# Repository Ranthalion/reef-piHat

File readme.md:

View this project on [CADLAB.io](https://cadlab.io/project/1832). 

# reef-piHat
RPI Hat for reef-pi

Supports
 - Back powering the rpi with 5v
 - 9 channels of PWM control via PCA9685 (split between 3 connectors)
 - 3 channels for 1 wire communication (up to 3 DS18B20 temperature probes)
 - 2 i2c ports for ph probe modules
 - 2 ATO sensors
 - 8 channel 12v relay control via ULN2803
 - 8 GPIO breakout (intended for 3.3v relay module)

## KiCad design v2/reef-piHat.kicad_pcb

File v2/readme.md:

# reef-piHat
RPI Hat for reef-pi

Supports
 - Back powering the rpi with 5v
 - 12 channels of PWM control via PCA9685 (split between 4 connectors) with address selection
 - 3 channels for 1 wire communication (up to 3 DS18B20 temperature probes)
 - 2 i2c ports for ph probe modules
 - 2 ATO sensors with input protection
 - 8 channel 12v relay control via ULN2803
 - 8 GPIO breakout with input and output protection

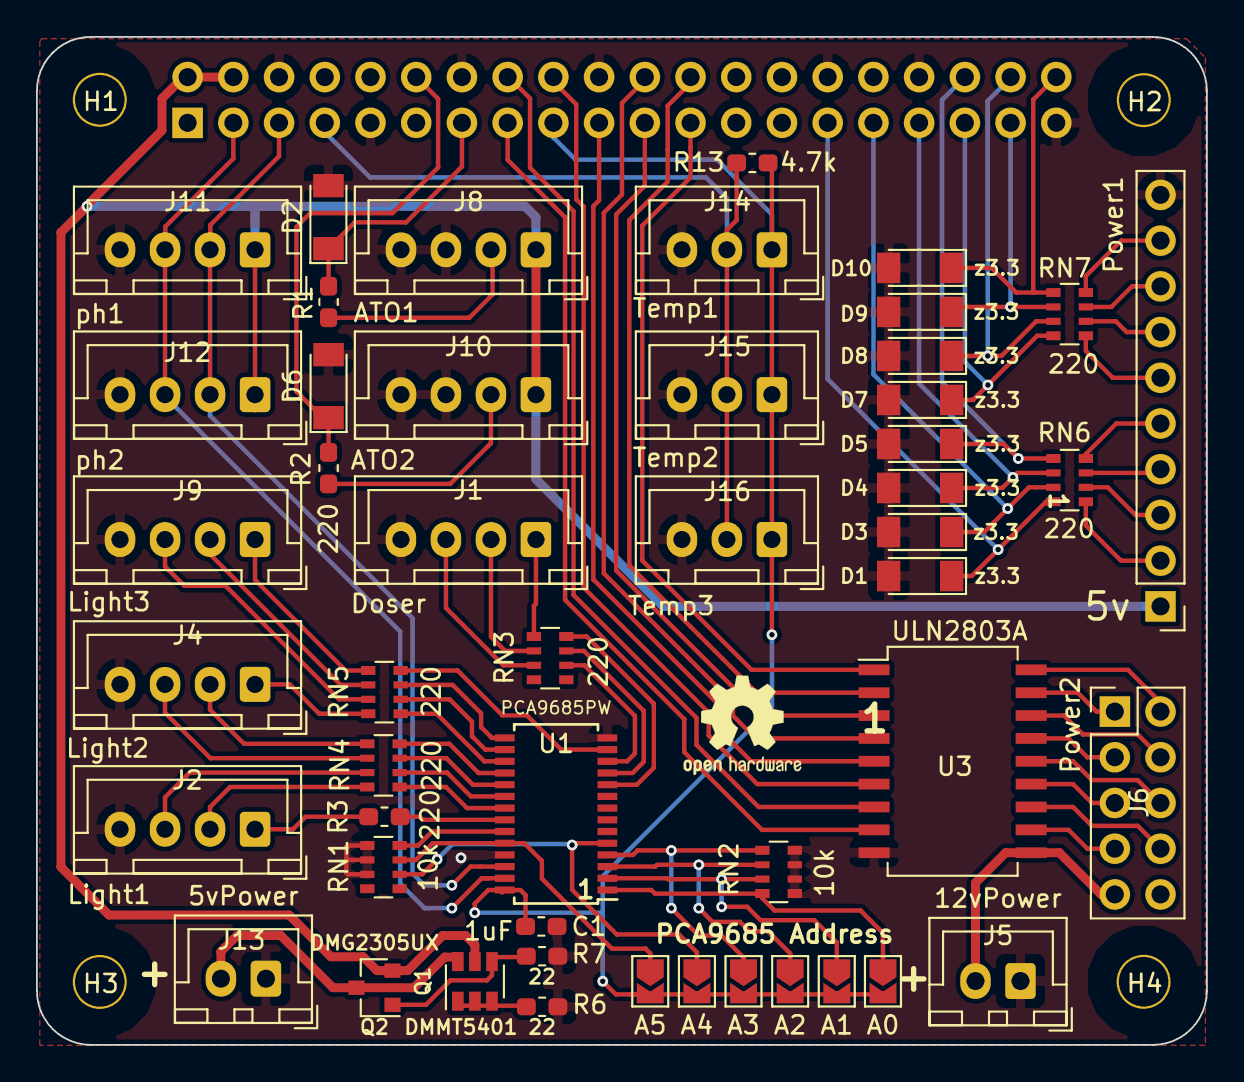
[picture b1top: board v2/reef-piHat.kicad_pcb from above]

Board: 2 copper layers, 65.0 x 56.0 mm, 54 parts (1 on the bottom side), 77 nets.

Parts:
A0, A1, A2, A3, A4, A5: NO; SolderJumper-2_P1.3mm_Open_TrianglePad1.0x1.5mm
C1: 1uF; C_0603_1608Metric_Pad1.05x0.95mm_HandSolder
D1, D2, D3, D4, D5, D6, D7, D8, D9, D10: z3.3; D_MiniMELF
H1, H2, H3, H4: 3mm_Mounting_Hole; NPTH_3mm_ID
J1: Doser; JST_XH_B04B-XH-A_1x04_P2.50mm_Vertical
J2: Light1; JST_XH_B04B-XH-A_1x04_P2.50mm_Vertical
J3: 40HAT; PinSocket_2x20_P2.54mm_Vertical
J4: Light2; JST_XH_B04B-XH-A_1x04_P2.50mm_Vertical
J5: 12vPower; JST_XH_B02B-XH-A_1x02_P2.50mm_Vertical
J6: Power2; PinHeader_2x05_P2.54mm_Vertical
J7: Power1; PinHeader_1x10_P2.54mm_Vertical
J8: ATO1; JST_XH_B04B-XH-A_1x04_P2.50mm_Vertical
J9: Light3; JST_XH_B04B-XH-A_1x04_P2.50mm_Vertical
J10: ATO2; JST_XH_B04B-XH-A_1x04_P2.50mm_Vertical
J11: ph1; JST_XH_B04B-XH-A_1x04_P2.50mm_Vertical
J12: ph2; JST_XH_B04B-XH-A_1x04_P2.50mm_Vertical
J13: 5vPower; JST_XH_B02B-XH-A_1x02_P2.50mm_Vertical
J14: Temp1; JST_XH_B03B-XH-A_1x03_P2.50mm_Vertical
J15: Temp2; JST_XH_B03B-XH-A_1x03_P2.50mm_Vertical
J16: Temp3; JST_XH_B03B-XH-A_1x03_P2.50mm_Vertical
Q1: DMMT5401; SOT-23-6
Q2: DMG2305UX; SOT-23
R1, R2, R3: 220; R_0603_1608Metric_Pad1.05x0.95mm_HandSolder
R6, R7: 22; R_0603_1608Metric_Pad1.05x0.95mm_HandSolder
R13: 4.7k; R_0603_1608Metric_Pad1.05x0.95mm_HandSolder
RN1, RN2: 10k; R_Array_Convex_4x0603
RN3, RN4, RN5, RN6, RN7: 220; R_Array_Convex_4x0603
U1: PCA9685PW; TSSOP-28_4.4x9.7mm_P0.65mm
U3: ULN2803A; SOP-18_7.0x12.5mm_P1.27mm

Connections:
/1WIRE: J3.7, J14.2, J15.2, J16.2, R13.1
/12V: J5.1, J6.9, U3.10
/A0: A0.1, RN2.8, U1.1
/A1: A1.1, RN2.7, U1.2
/A2: A2.1, RN2.6, U1.3
/A3: A3.1, RN2.5, U1.4
/A4: A4.1, RN1.6, U1.5
/A5: A5.1, RN1.7, U1.24
/ATO1: D2.1, J3.13, R1.2
/ATO2: D6.1, J3.12, R2.2
/LED4: RN3.8, U1.10
/LED5: RN3.7, U1.11
/LED6: RN3.6, U1.12
/LED7: RN5.8, U1.13
/LED8: RN5.7, U1.15
/LED9: RN5.6, U1.16
/LED10: RN5.5, U1.17
/LED11: RN4.8, U1.18
/LED12: RN4.7, U1.19
/LED13: RN4.6, U1.20
/LED14: RN4.5, U1.21
/LED15: R3.1, U1.22
/OE: RN1.8, U1.23
/P3V3_HAT: A0.2, A1.2, A2.2, A3.2, A4.2, A5.2, C1.1, J3.17, J14.1, J15.1, J16.1, R13.2, U1.28
/P5V: J13.2, Q1.6, Q2.3
/P5V_HAT: J3.2, J3.4, J7.1, J8.1, J10.1, J11.1, J12.1, Q1.5, Q2.2
/PA1: J3.23, U3.1
/PA2: J3.24, U3.2
/PA3: J3.21, U3.3
/PA4: J3.22, U3.4
/PA5: J3.19, U3.5
/PA6: J3.18, U3.6
/PA7: J3.16, U3.7
/PA8: J3.15, U3.8
/PA_O1: J6.2, U3.18
/PA_O2: J6.1, U3.17
/PA_O3: J6.4, U3.16
/PA_O4: J6.3, U3.15
/PA_O5: J6.6, U3.14
/PA_O6: J6.5, U3.13
/PA_O7: J6.8, U3.12
/PA_O8: J6.7, U3.11
/PB1: D10.1, J3.40, RN7.1
/PB2: D9.1, J3.37, RN7.2
/PB3: D8.1, J3.38, RN7.3
/PB4: D7.1, J3.35, RN7.4
/PB5: D5.1, J3.36, RN6.1
/PB6: D4.1, J3.33, RN6.2
/PB7: D3.1, J3.31, RN6.3
/PB8: D1.1, J3.29, RN6.4
/SCL: J3.5, J11.2, J12.2, U1.26
/SDA: J3.3, J11.3, J12.3, U1.27
GND: C1.2, D1.2, D2.2, D3.2, D4.2, D5.2, D6.2, D7.2, D8.2, D9.2, D10.2, J1.4, J2.4, J3.6, J3.9, J3.14, J3.20, J3.25, J3.30, J3.34, J3.39, J4.4, J5.2, J7.10, J8.3, J8.4, J9.4, J10.3, J10.4, J11.4, J12.4, J13.1, J14.3, J15.3, J16.3, R6.2, R7.2, RN1.1, RN1.2, RN1.3, RN2.1, RN2.2, RN2.3, RN2.4, U1.14, U1.25, U3.9
unnamed: J1.1, RN3.1
unnamed: J1.2, RN3.2
unnamed: J1.3, RN3.3
unnamed: J2.1, R3.2
unnamed: J2.2, RN4.4
unnamed: J2.3, RN4.3
unnamed: J4.1, RN5.4
unnamed: J4.2, RN4.1
unnamed: J4.3, RN4.2
unnamed: J7.2, RN6.5
unnamed: J7.3, RN6.6
unnamed: J7.4, RN6.7
unnamed: J7.5, RN6.8
unnamed: J7.6, RN7.5
unnamed: J7.7, RN7.6
unnamed: J7.8, RN7.7
unnamed: J7.9, RN7.8
unnamed: J8.2, R1.1
unnamed: J9.1, RN5.1
unnamed: J9.2, RN5.2
unnamed: J9.3, RN5.3
unnamed: J10.2, R2.1
unnamed: Q1.1, Q1.2, Q1.3, R6.1
unnamed: Q1.4, Q2.1, R7.1

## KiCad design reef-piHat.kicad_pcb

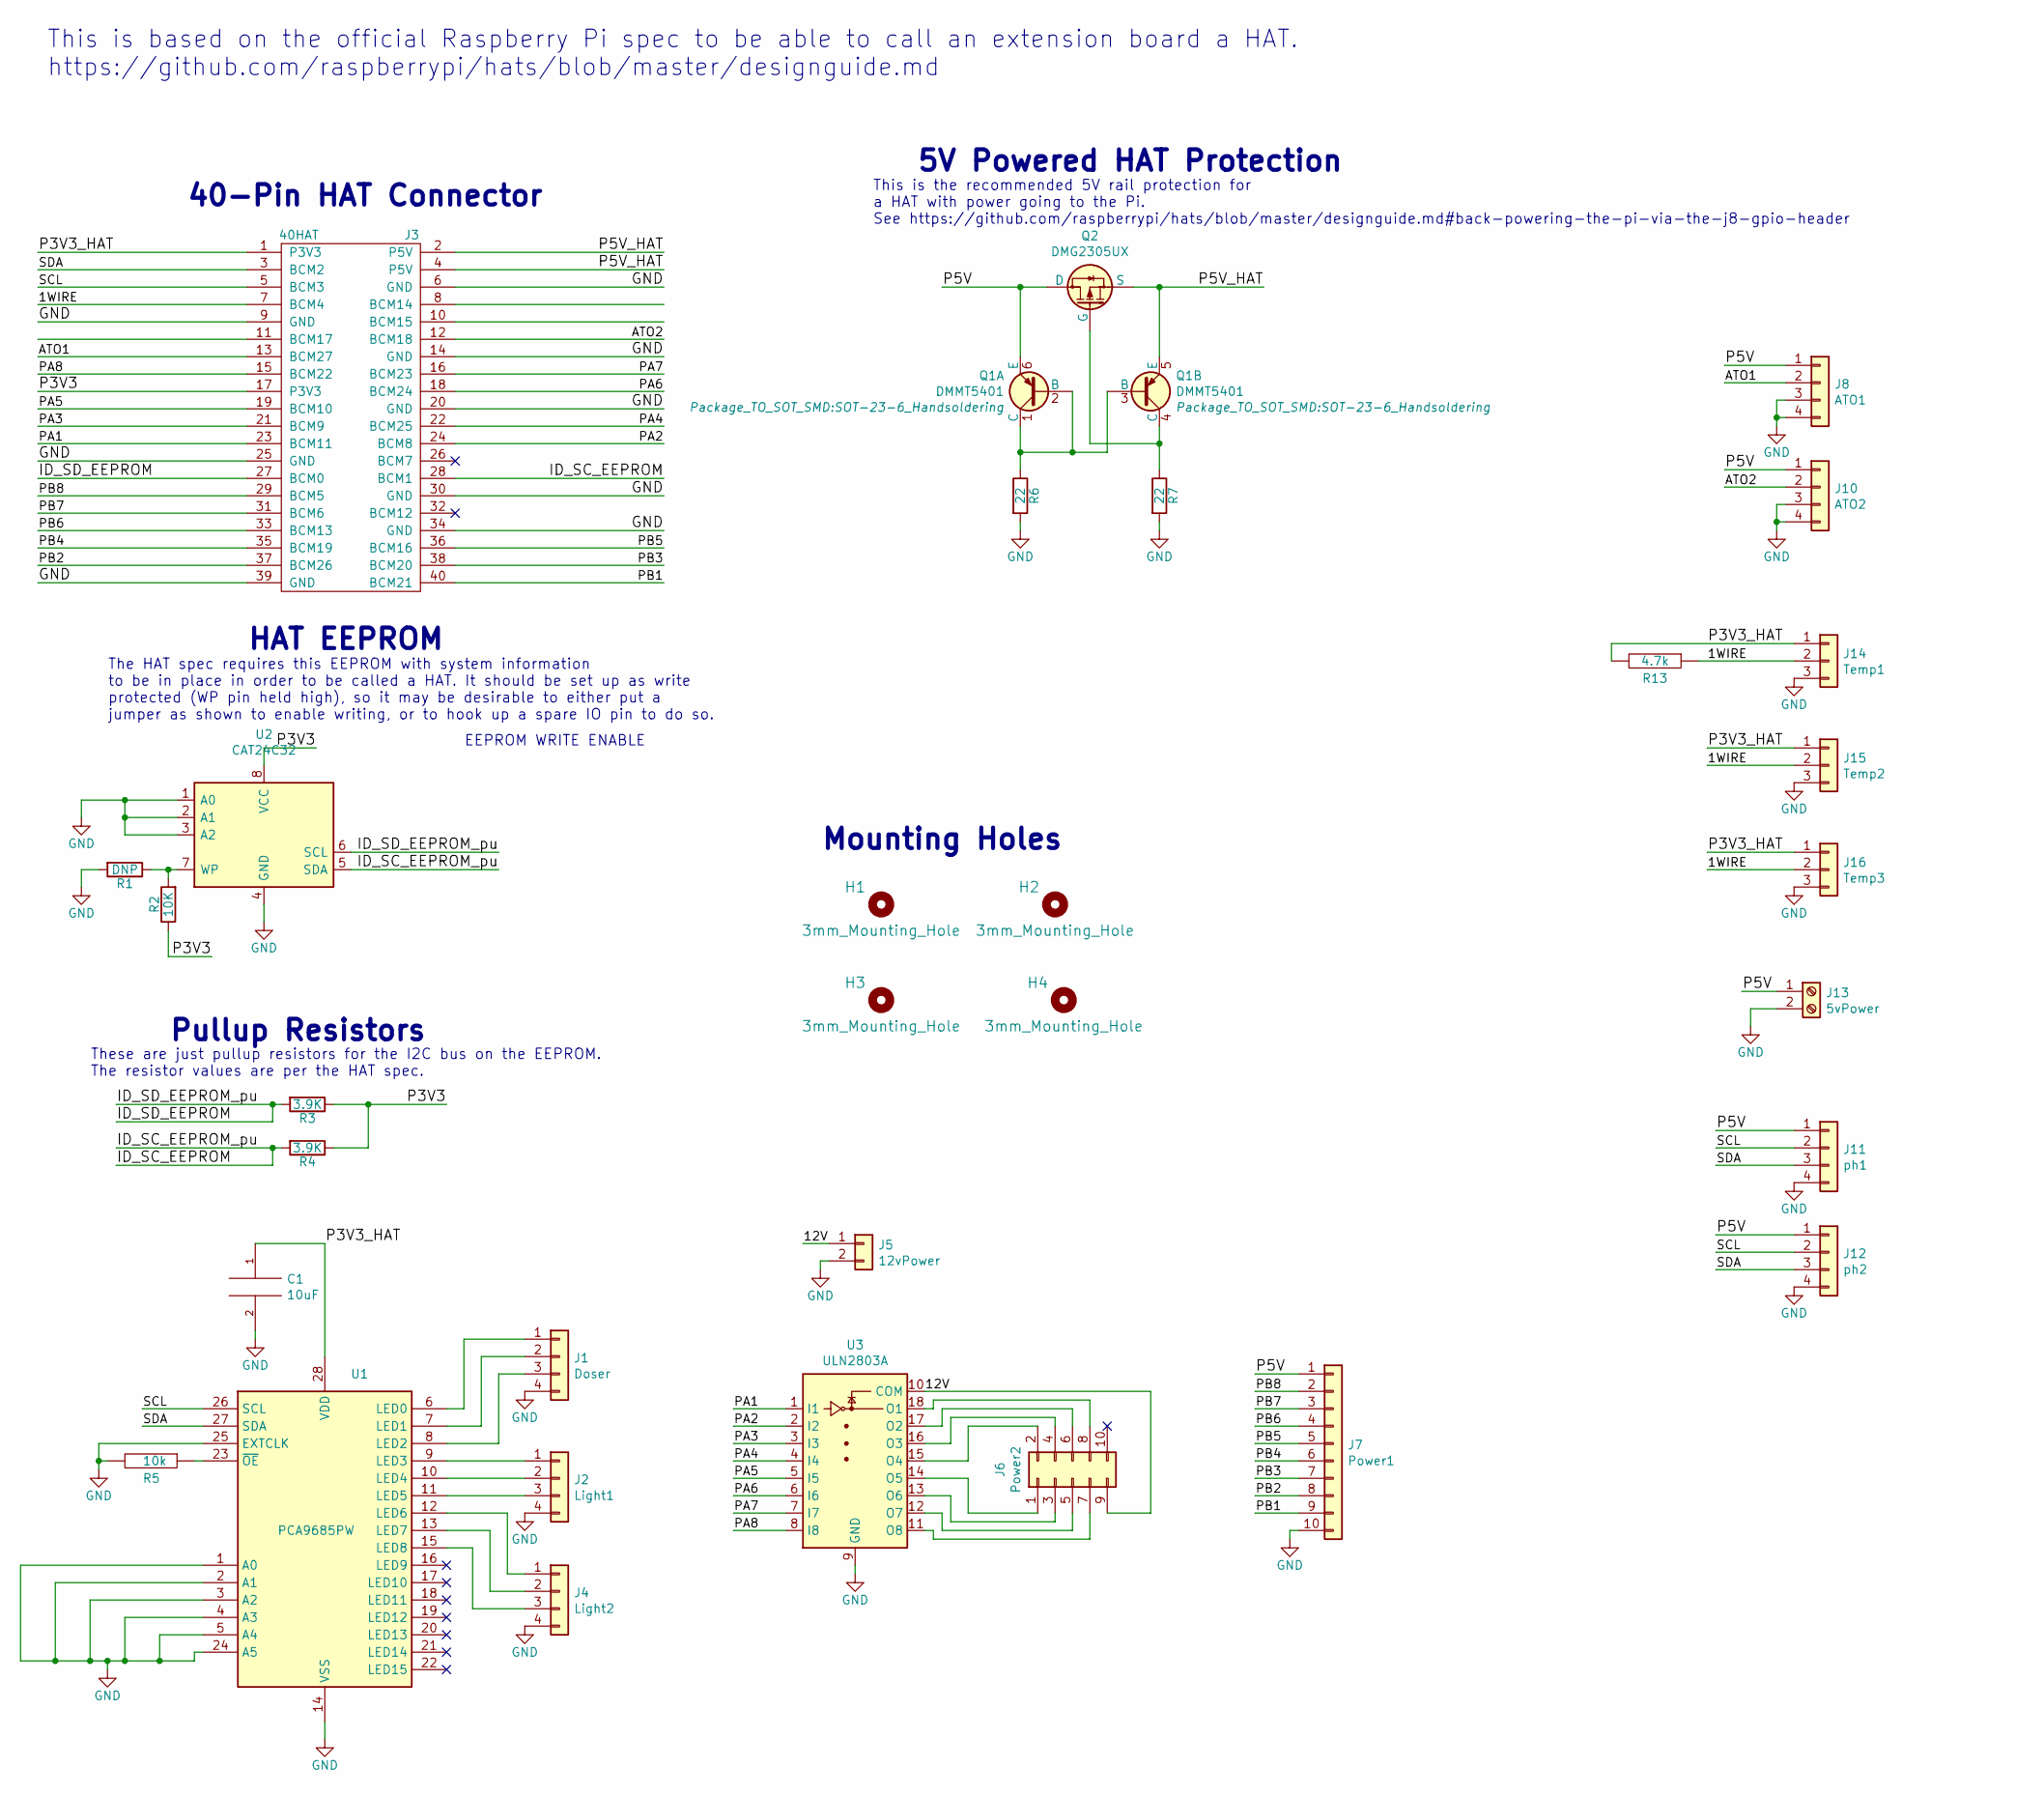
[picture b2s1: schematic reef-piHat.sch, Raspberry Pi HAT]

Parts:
C1: 10uF; C_1206_3216Metric_Pad1.42x1.75mm_HandSolder
H1, H2, H3, H4: 3mm_Mounting_Hole; NPTH_3mm_ID
J1: Doser; JST_XH_B04B-XH-A_1x04_P2.50mm_Vertical
J2: Light1; JST_XH_B04B-XH-A_1x04_P2.50mm_Vertical
J3: 40HAT; PinSocket_2x20_P2.54mm_Vertical
J4: Light2; JST_XH_B04B-XH-A_1x04_P2.50mm_Vertical
J5: 12vPower; PinHeader_1x02_P2.54mm_Vertical
J6: Power2; PinHeader_2x05_P2.54mm_Vertical
J7: Power1; PinHeader_1x10_P2.54mm_Vertical
J8: ATO1; JST_XH_B04B-XH-A_1x04_P2.50mm_Vertical
J10: ATO2; JST_XH_B04B-XH-A_1x04_P2.50mm_Vertical
J11: ph1; JST_XH_B04B-XH-A_1x04_P2.50mm_Vertical
J12: ph2; JST_XH_B04B-XH-A_1x04_P2.50mm_Vertical
J13: 5vPower; PinHeader_1x02_P2.54mm_Vertical
J14: Temp1; JST_XH_B03B-XH-A_1x03_P2.50mm_Vertical
J15: Temp2; JST_XH_B03B-XH-A_1x03_P2.50mm_Vertical
J16: Temp3; JST_XH_B03B-XH-A_1x03_P2.50mm_Vertical
Q1: DMMT5401; SOT-23-6_Handsoldering
Q2: DMG2305UX; SOT-23_Handsoldering
R1: DNP; R_0603_1608Metric_Pad1.05x0.95mm_HandSolder; MPN RC0402JR-0722RL
R2: 10K; R_0603_1608Metric_Pad1.05x0.95mm_HandSolder; MPN RC0402JR-0722RL
R3, R4: 3.9K; R_0603_1608Metric_Pad1.05x0.95mm_HandSolder; MPN RC0402JR-0722RL
R5: 10k; R_0603_1608Metric_Pad1.05x0.95mm_HandSolder
R6, R7: 22; R_0603_1608Metric_Pad1.05x0.95mm_HandSolder; MPN RC0402JR-0722RL
R13: 4.7k; R_0603_1608Metric_Pad1.05x0.95mm_HandSolder
U1: PCA9685PW; TSSOP-28_4.4x9.7mm_P0.65mm
U2: CAT24C32; SOIC-8_3.9x4.9mm_P1.27mm
U3: ULN2803A; SOP-18_7.0x12.5mm_P1.27mm

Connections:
/1WIRE: J3.7 (BCM4), J14.2, J15.2, J16.2, R13.1
/12V: J5.1, J6.9, U3.10 (COM)
/ATO1: J3.13 (BCM27), J8.2
/ATO2: J3.12 (BCM18), J10.2
/ID_SC_EEPROM: J3.28 (BCM1), R4.2, U2.5 (SDA)
/ID_SD_EEPROM: J3.27 (BCM0), R3.2, U2.6 (SCL)
/P3V3: J3.17 (P3V3), R2.1, R3.1, R4.1, U2.8 (VCC)
/P3V3_HAT: C1.1, J3.1 (P3V3), J14.1, J15.1, J16.1, R13.2, U1.28 (VDD)
/P5V: J7.1, J8.1, J10.1, J11.1, J12.1, J13.1, Q1.6 (E), Q2.3 (D)
/P5V_HAT: J3.2 (P5V), J3.4 (P5V), Q1.5 (E), Q2.2 (S)
/PA1: J3.23 (BCM11), U3.1 (I1)
/PA2: J3.24 (BCM8), U3.2 (I2)
/PA3: J3.21 (BCM9), U3.3 (I3)
/PA4: J3.22 (BCM25), U3.4 (I4)
/PA5: J3.19 (BCM10), U3.5 (I5)
/PA6: J3.18 (BCM24), U3.6 (I6)
/PA7: J3.16 (BCM23), U3.7 (I7)
/PA8: J3.15 (BCM22), U3.8 (I8)
/PB1: J3.40 (BCM21), J7.9
/PB2: J3.37 (BCM26), J7.8
/PB3: J3.38 (BCM20), J7.7
/PB4: J3.35 (BCM19), J7.6
/PB5: J3.36 (BCM16), J7.5
/PB6: J3.33 (BCM13), J7.4
/PB7: J3.31 (BCM6), J7.3
/PB8: J3.29 (BCM5), J7.2
/SCL: J3.5 (BCM3), J11.2, J12.2, U1.26 (SCL)
/SDA: J3.3 (BCM2), J11.3, J12.3, U1.27 (SDA)
GND: C1.2, J1.4, J2.4, J3.6 (GND), J3.9 (GND), J3.14 (GND), J3.20 (GND), J3.25 (GND), J3.30 (GND), J3.34 (GND), J3.39 (GND), J4.4, J5.2, J7.10, J8.3, J8.4, J10.3, J10.4, J11.4, J12.4, J13.2, J14.3, J15.3, J16.3, R1.2, R5.2, R6.2, R7.2, U1.1 (A0), U1.2 (A1), U1.3 (A2), U1.4 (A3), U1.5 (A4), U1.14 (VSS), U1.24 (A5), U1.25 (EXTCLK), U2.1 (A0), U2.2 (A1), U2.3 (A2), U2.4 (GND), U3.9 (GND)
unnamed: J1.1, U1.6 (LED0)
unnamed: J1.2, U1.7 (LED1)
unnamed: J1.3, U1.8 (LED2)
unnamed: J2.1, U1.9 (LED3)
unnamed: J2.2, U1.10 (LED4)
unnamed: J2.3, U1.11 (LED5)
unnamed: J4.1, U1.12 (LED6)
unnamed: J4.2, U1.13 (LED7)
unnamed: J4.3, U1.15 (LED8)
unnamed: J6.1, U3.14 (O5)
unnamed: J6.2, U3.15 (O4)
unnamed: J6.3, U3.13 (O6)
unnamed: J6.4, U3.16 (O3)
unnamed: J6.5, U3.12 (O7)
unnamed: J6.6, U3.17 (O2)
unnamed: J6.7, U3.11 (O8)
unnamed: J6.8, U3.18 (O1)
unnamed: Q1.1 (C), Q1.2 (B), Q1.3 (B), R6.1
unnamed: Q1.4 (C), Q2.1 (G), R7.1
unnamed: R1.1, R2.2, U2.7 (WP)
unnamed: R5.1, U1.23 (~OE)

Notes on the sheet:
Mounting Holes
40-Pin HAT Connector
This is based on the official Raspberry Pi spec to be able to call an extension board a HAT. https://github.com/raspberrypi/hats/blob/master/designguide.md
EEPROM WRITE ENABLE
Pullup Resistors
HAT EEPROM
The HAT spec requires this EEPROM with system information to be in place in order to be called a HAT. It should be set up as write protected (WP pin held high), so it may be desirable to either put a jumper as shown to enable writing, or to hook up a spare IO pin to do so.
These are just pullup resistors for the I2C bus on the EEPROM. The resistor values are per the HAT spec.
5V Powered HAT Protection
This is the recommended 5V rail protection for a HAT with power going to the Pi. See https://github.com/raspberrypi/hats/blob/master/designguide.md#back-powering-the-pi-via-the-j8-gpio-header

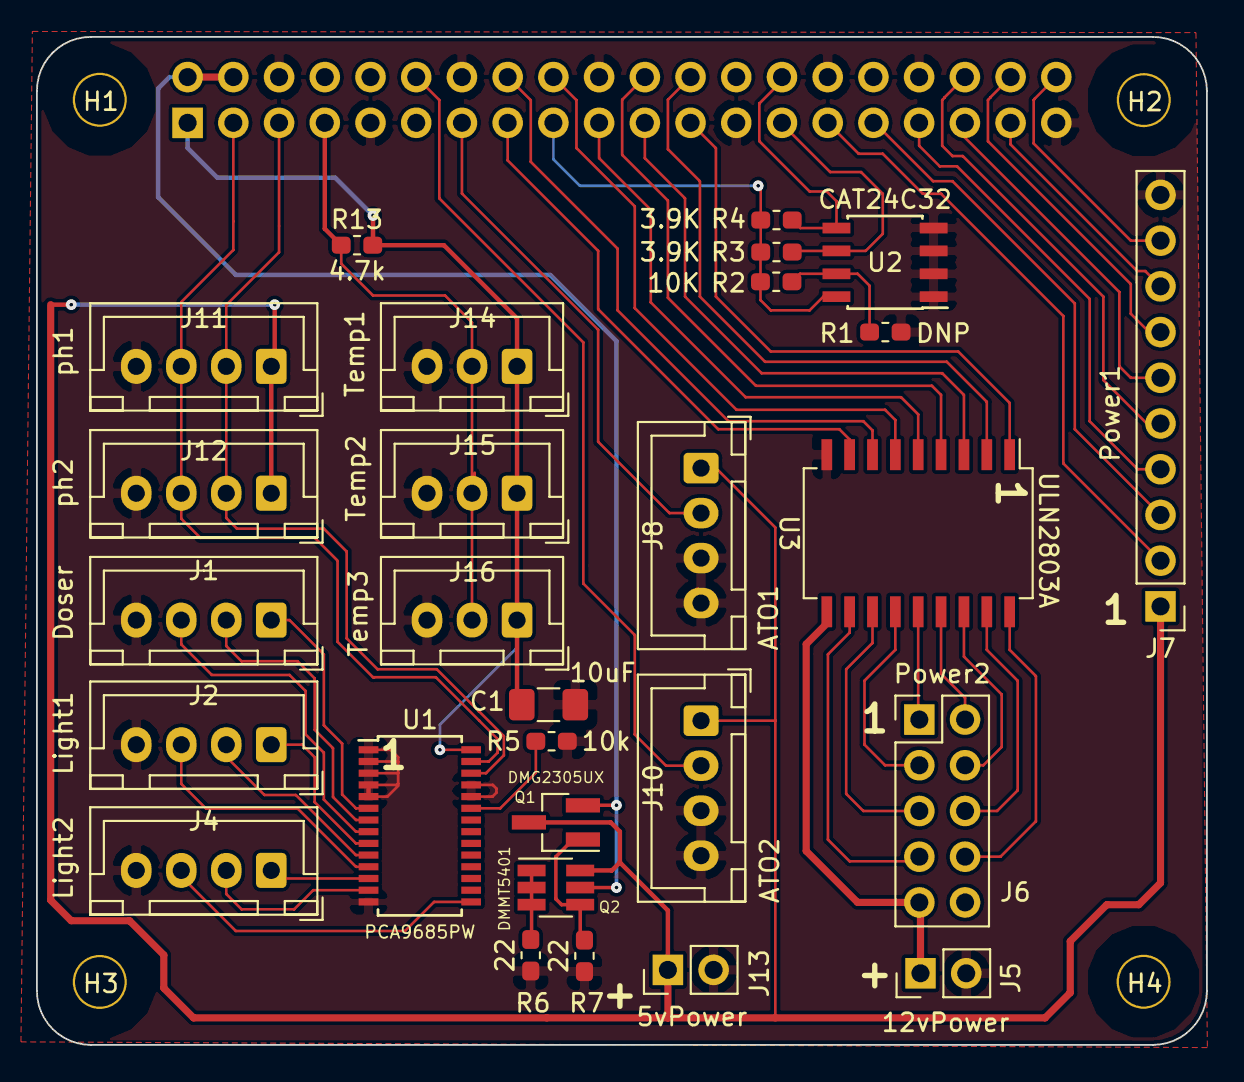
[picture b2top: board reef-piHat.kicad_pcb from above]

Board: 2 copper layers, 65.0 x 56.0 mm, 33 parts (1 on the bottom side), 50 nets.

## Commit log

2018-11-18 Schematic and PCB for reef-pi hat
2018-11-21 Complete layout and update gerbers
2018-11-25 Add readme and images
2019-01-31 Initial v2 commit
2019-02-10 v2 design
2019-02-12 Gerbers
2019-02-15 update images
2019-02-15 update readme images
2019-02-21 update readme for v2
2019-03-05 v3 schematic and layout
2019-03-09 add v3 gerbers
2019-06-06 Backlink to CADLAB.io has been added.
2022-01-16 Update gerbers
